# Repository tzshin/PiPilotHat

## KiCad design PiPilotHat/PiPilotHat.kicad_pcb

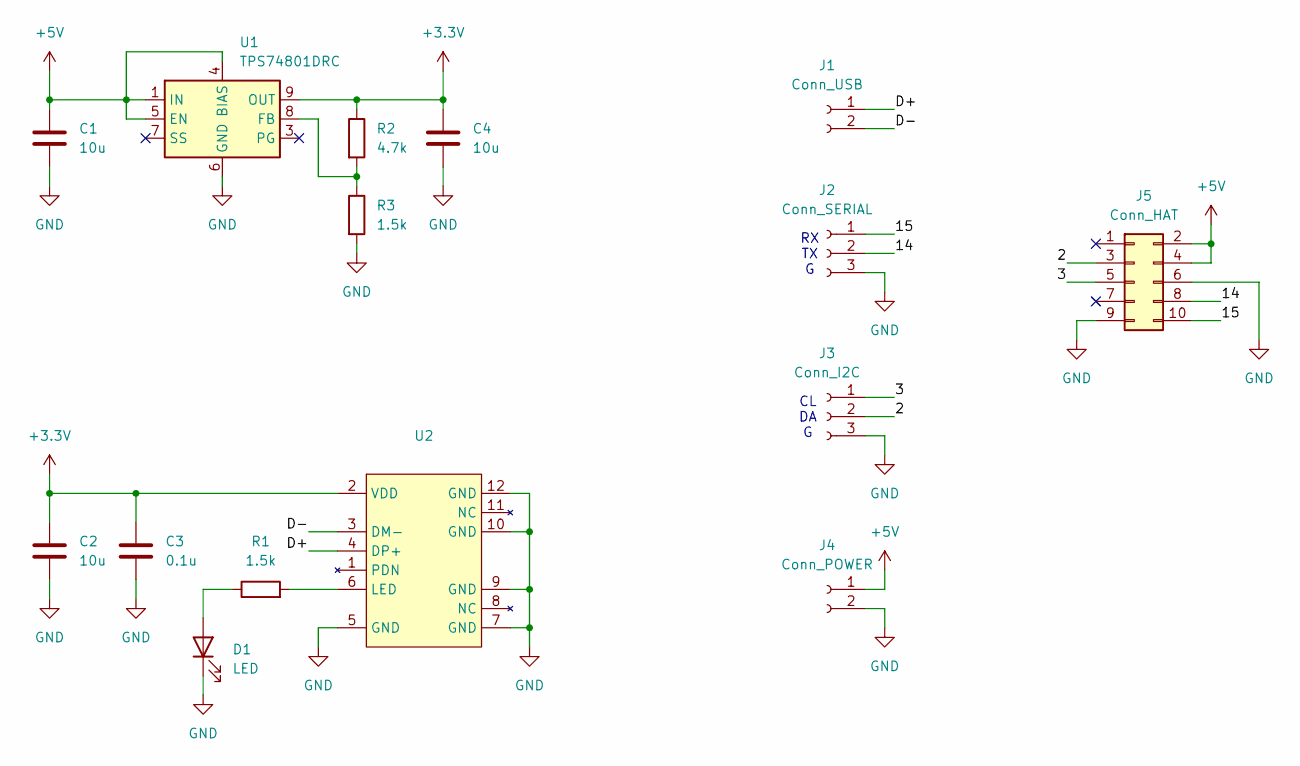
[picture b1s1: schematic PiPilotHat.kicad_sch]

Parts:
C1, C2, C4: 10u; C_0805_2012Metric
C3: 0.1u; C_0805_2012Metric
D1: LED; LED_0805_2012Metric
J1: Conn_USB; USB_Data
J2: Conn_SERIAL; JST_ZH_1x03_Simple
J3: Conn_I2C; JST_ZH_1x03_Simple
J4: Conn_POWER; JST_ZH_1x02_Simple
J5: Conn_HAT; PinSocket_2x05_P2.54mm_Vertical
R1, R3: 1.5k; R_0805_2012Metric
R2: 4.7k; R_0805_2012Metric
U1: TPS74801DRC; VSON-10-1EP_3x3mm_P0.5mm_EP1.65x2.4mm_ThermalVias
U2: PL-R8812AF1; BL-R8812AF1

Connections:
+3.3V: C2.1, C3.1, C4.1, R2.1, U1.9 (OUT), U1.10 (OUT), U2.2 (VDD)
+5V: C1.1, J4.1, J5.2, J5.4, U1.1 (IN), U1.2 (IN), U1.4 (BIAS), U1.5 (EN)
/2: J3.2, J5.3
/3: J3.1, J5.5
/14: J2.2, J5.8
/15: J2.1, J5.10
/D+: J1.1, U2.4 (DP+)
/D-: J1.2, U2.3 (DM-)
GND: C1.2, C2.2, C3.2, C4.2, D1.1 (K), J2.3, J3.3, J4.2, J5.6, J5.9, R3.2, U1.6 (GND), U1.11 (GND), U2.5 (GND), U2.7 (GND), U2.9 (GND), U2.10 (GND), U2.12 (GND)
unnamed: D1.2 (A), R1.1
unnamed: R2.2, R3.1, U1.8 (FB)
unnamed: R1.2, U2.6 (LED)

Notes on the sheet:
RX TX G
CL DA G

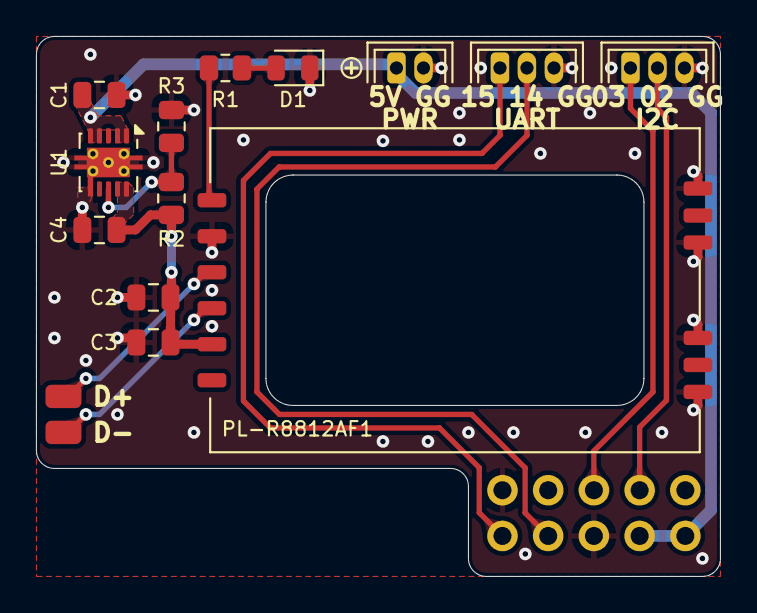
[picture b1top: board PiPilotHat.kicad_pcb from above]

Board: 2 copper layers, 38.0 x 30.0 mm, 15 parts (1 on the bottom side), 12 nets.
